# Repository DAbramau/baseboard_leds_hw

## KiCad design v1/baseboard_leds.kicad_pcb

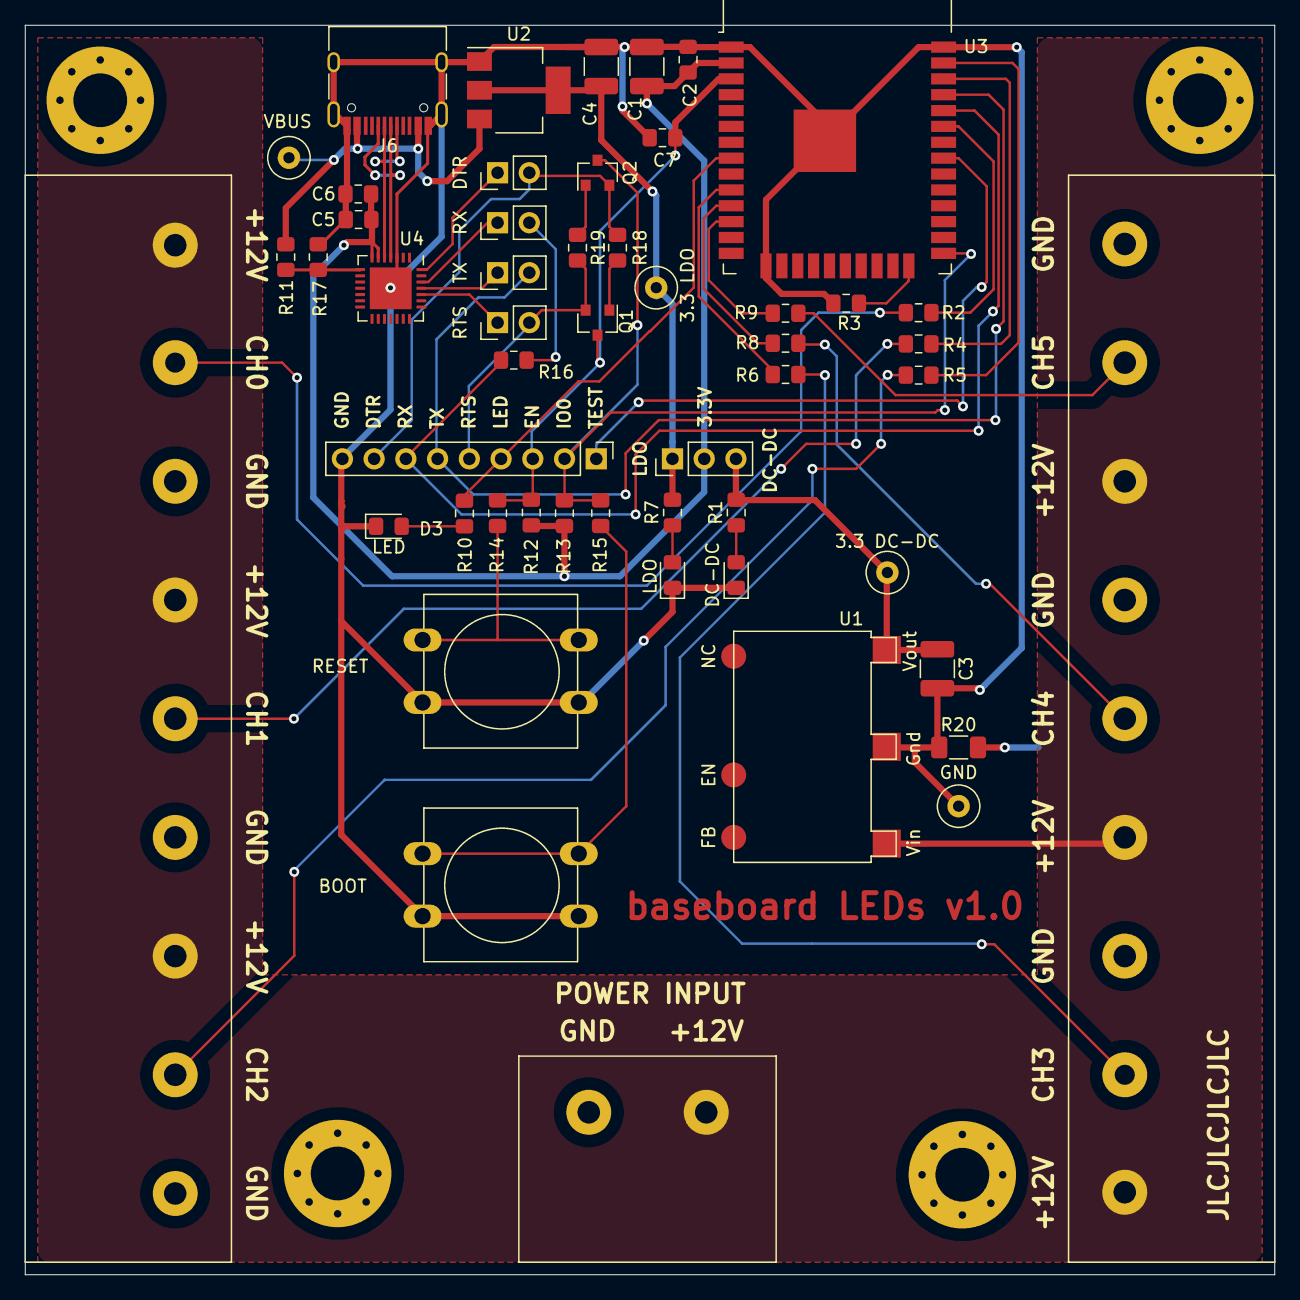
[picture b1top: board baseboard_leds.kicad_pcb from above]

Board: 2 copper layers, 100.0 x 100.0 mm, 56 parts (0 on the bottom side), 43 nets.

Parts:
C1, C3, C4: 100uF; C_1210_3225Metric_Pad1.33x2.70mm_HandSolder
C2: 1uF; C_0805_2012Metric_Pad1.15x1.40mm_HandSolder
C5: 0.1uF; C_0805_2012Metric_Pad1.15x1.40mm_HandSolder
C6: 10uF; C_0805_2012Metric_Pad1.15x1.40mm_HandSolder
C7: 1nF; C_0805_2012Metric_Pad1.15x1.40mm_HandSolder
D1, D2, D3: LED; LED_0805_2012Metric_Pad1.15x1.40mm_HandSolder
H1, H2, H3, H4: MountingHole_Pad; MountingHole_4.3mm_M4_Pad_Via
J1, J2: Conn_01x09; HB9500-9
J3: Conn_01x02; HB9500-2
J5: Conn_01x09; PinHeader_1x09_P2.54mm_Vertical
J6: USB_C_Receptacle_USB2.0; USB_C_Receptacle_HRO_TYPE-C-31-M-12
JP1: Jumper_3_Bridged12; PinHeader_1x03_P2.54mm_Vertical
JP2, JP3, JP4, JP5: Jumper_NC_Small; PinHeader_1x02_P2.54mm_Vertical
Q1, Q2: MMBT3904; SOT-23
R1, R7, R10: 100; R_0805_2012Metric_Pad1.15x1.40mm_HandSolder
R2, R4, R5, R6, R8, R9, R14, R15, R16: 470; R_0805_2012Metric_Pad1.15x1.40mm_HandSolder
R3, R13: 5K; R_0805_2012Metric_Pad1.15x1.40mm_HandSolder
R11: 24K; R_0805_2012Metric_Pad1.15x1.40mm_HandSolder
R12, R18, R19: 12K; R_0805_2012Metric_Pad1.15x1.40mm_HandSolder
R17: 47K; R_0805_2012Metric_Pad1.15x1.40mm_HandSolder
R20: 0; R_1206_3216Metric_Pad1.30x1.75mm_HandSolder
SW1, SW2: SW_Push; SW_PUSH-12mm
TP1, TP2, TP3, TP4: TestPoint; TestPoint_Loop_D2.60mm_Drill0.9mm_Beaded
U1: MP2225_DC_DC_module
U2: AMS1117-3.3; SOT-223-3_TabPin2
U3: ESP32-WROOM-32D; ESP32-WROOM-32
U4: CP2102N-A01-GQFN28; QFN-28-1EP_5x5mm_P0.5mm_EP3.35x3.35mm

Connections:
+3V3: C1.1, C2.1, C5.1, C6.1, JP1.2, R12.1, R13.1, U3.2, U4.6, U4.7
+12V: J1.1, J1.4, J1.7, J2.1, J2.4, J2.7, J3.2, U1.1
/3.3_dc-dc: C3.1, JP1.3, R1.2, TP1.1, U1.3
/3.3_ldo: C4.1, JP1.1, R7.2, TP3.1, U2.2
/CH0: R2.2, U3.33
/CH1: R4.2, U3.36
/CH2: R5.2, U3.37
/CH3: R6.2, U3.10
/CH4: R8.2, U3.11
/CH5: R9.2, U3.12
/CH_0: J1.2, R2.1
/CH_1: J1.5, R4.1
/CH_2: J1.8, R5.1
/CH_3: J2.2, R6.1
/CH_4: J2.5, R8.1
/CH_5: J2.8, R9.1
/DTR: J5.8, JP5.2, Q2.2, R18.2
/EN: C7.1, J5.3, Q1.3, R12.2, R14.2, U3.3
/IO0: J5.2, Q2.3, R13.2, R15.2, U3.25
/LED: J5.4, R10.2, U3.8
/MCU_RX: J5.7, R16.1, U3.34
/MCU_TX: J5.6, JP3.2, U3.35
/RTS: J5.5, JP2.2, Q1.2, R19.2
/TST: J5.1, U3.31
/USB_DM: J6.A7, J6.B7, U4.5
/USB_DP: J6.A6, J6.B6, U4.4
GND: J1.3, J1.6, J1.9, J2.3, J2.6, J2.9, J3.1, R20.2
GNDD: C1.2, C2.2, C3.2, C4.2, C5.2, C6.2, C7.2, D1.1, D2.1, D3.1, J5.9, J6.A1, J6.A12, J6.B1, J6.B12, J6.S1, R3.1, R17.2, R20.1, SW1.2, SW2.2, TP4.1, U1.2, U2.1, U3.1, U3.15, U3.38, U3.39, U4.3, U4.29
unnamed: D1.2, R1.1
unnamed: D2.2, R7.1
unnamed: D3.2, R10.1
unnamed: JP2.1, U4.24
unnamed: JP3.1, U4.25
unnamed: JP4.1, U4.26
unnamed: JP4.2, R16.2
unnamed: JP5.1, U4.28
unnamed: Q1.1, R18.1
unnamed: Q2.1, R19.1
unnamed: R3.2, U3.24
unnamed: R11.2, R17.1, U4.8
unnamed: R14.1, SW1.1
unnamed: R15.1, SW2.1
VBUS: J6.A4, J6.A9, J6.B4, J6.B9, R11.1, TP2.1, U2.3

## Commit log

2021-09-05 v1.0
